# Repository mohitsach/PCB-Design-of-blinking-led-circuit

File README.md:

# PCB Design of blinking led circuit in KiCad

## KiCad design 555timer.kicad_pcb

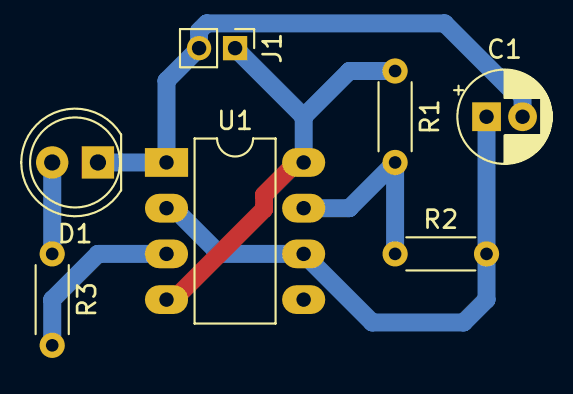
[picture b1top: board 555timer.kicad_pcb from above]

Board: 2 copper layers, 7 parts (0 on the bottom side), 6 nets.

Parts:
C1: 1u; CP_Radial_D5.0mm_P2.00mm
D1: LED; LED_D5.0mm
J1: POWER; PinHeader_1x02_P2.00mm_Vertical
R1, R3: 1k; R_Axial_DIN0204_L3.6mm_D1.6mm_P5.08mm_Horizontal
R2: 470k; R_Axial_DIN0204_L3.6mm_D1.6mm_P5.08mm_Horizontal
U1: LM555; DIP-8_W7.62mm_LongPads

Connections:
GND: C1.2, D1.1, J1.2, U1.1
unnamed: C1.1, R2.2, U1.2, U1.6
unnamed: D1.2, R3.1
unnamed: J1.1, R1.1, U1.4, U1.8
unnamed: R1.2, R2.1, U1.7
unnamed: R3.2, U1.3
